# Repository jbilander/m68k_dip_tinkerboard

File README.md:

# 68k_dip_tinkerboard
A tinkerboard for the old Motorola 68k CPU

***

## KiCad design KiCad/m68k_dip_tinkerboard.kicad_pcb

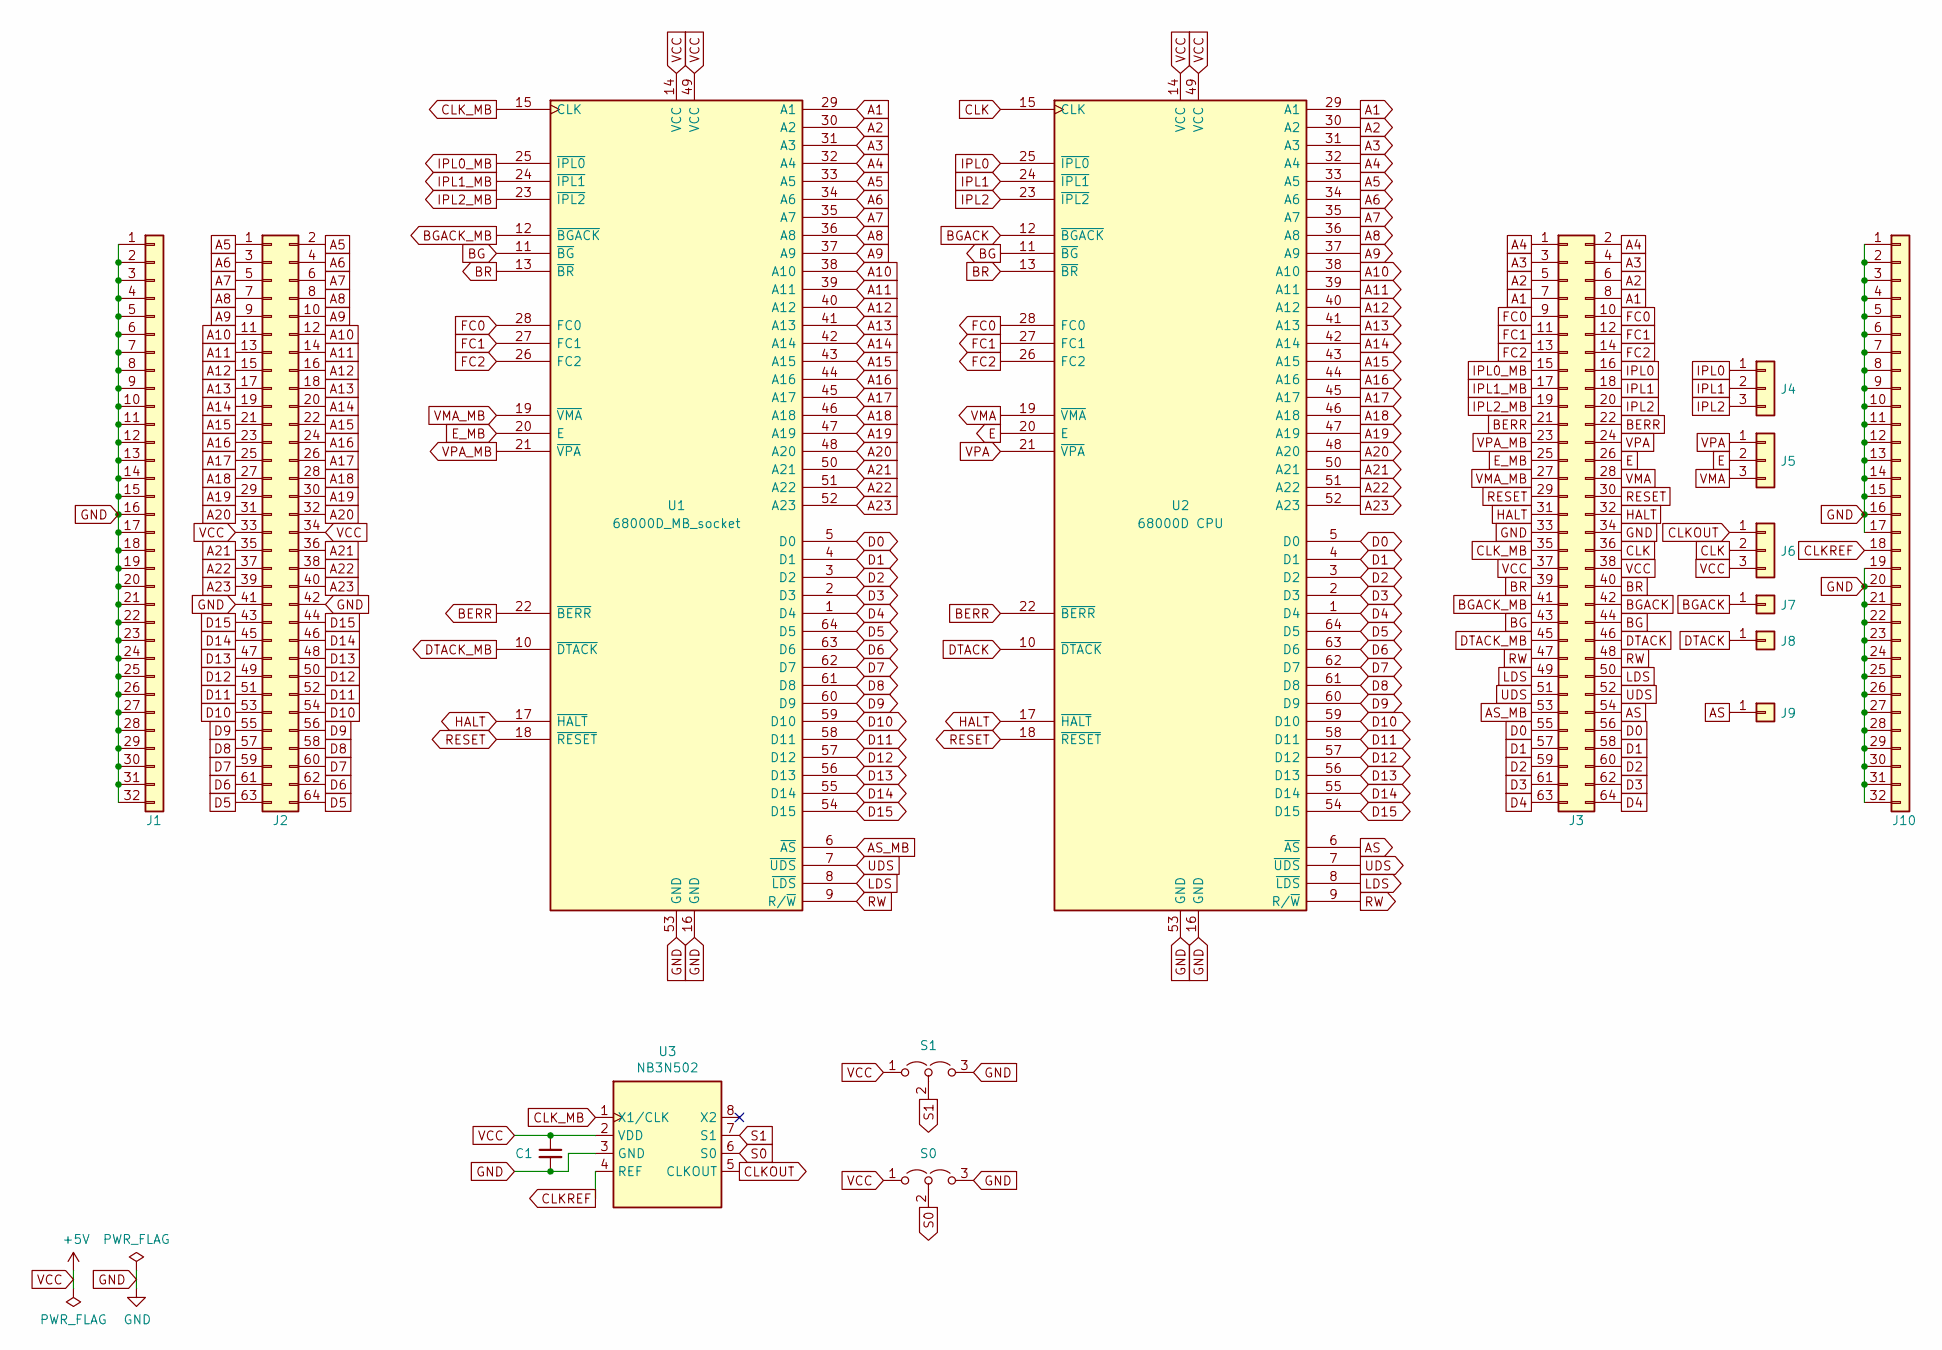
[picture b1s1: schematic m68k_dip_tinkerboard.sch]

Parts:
C1: C_Small; C_0805_2012Metric_Pad1.15x1.40mm_HandSolder
J1, J10: Conn_01x32; PinHeader_1x32_P2.54mm_Vertical
J2, J3: Conn_02x32_Odd_Even; PinHeader_2x32_P2.54mm_Vertical
J4, J5, J6: Conn_01x03; PinHeader_1x03_P2.54mm_Vertical
J7, J8, J9: Conn_01x01; PinHeader_1x01_P2.54mm_Vertical
S0, S1: Jumper_3_Open; PinHeader_1x03_P2.54mm_Vertical
U1: 68000D_MB_socket; DIP-64_W22.86mm_LongPads
U2: 68000D CPU; DIP-64_W22.86mm
U3: NB3N502; SOIC-8_3.9x4.9mm_P1.27mm

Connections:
A1: J3.7, J3.8, U1.29 (A1), U2.29 (A1)
A2: J3.5, J3.6, U1.30 (A2), U2.30 (A2)
A3: J3.3, J3.4, U1.31 (A3), U2.31 (A3)
A4: J3.1, J3.2, U1.32 (A4), U2.32 (A4)
A5: J2.1, J2.2, U1.33 (A5), U2.33 (A5)
A6: J2.3, J2.4, U1.34 (A6), U2.34 (A6)
A7: J2.5, J2.6, U1.35 (A7), U2.35 (A7)
A8: J2.7, J2.8, U1.36 (A8), U2.36 (A8)
A9: J2.9, J2.10, U1.37 (A9), U2.37 (A9)
A10: J2.11, J2.12, U1.38 (A10), U2.38 (A10)
A11: J2.13, J2.14, U1.39 (A11), U2.39 (A11)
A12: J2.15, J2.16, U1.40 (A12), U2.40 (A12)
A13: J2.17, J2.18, U1.41 (A13), U2.41 (A13)
A14: J2.19, J2.20, U1.42 (A14), U2.42 (A14)
A15: J2.21, J2.22, U1.43 (A15), U2.43 (A15)
A16: J2.23, J2.24, U1.44 (A16), U2.44 (A16)
A17: J2.25, J2.26, U1.45 (A17), U2.45 (A17)
A18: J2.27, J2.28, U1.46 (A18), U2.46 (A18)
A19: J2.29, J2.30, U1.47 (A19), U2.47 (A19)
A20: J2.31, J2.32, U1.48 (A20), U2.48 (A20)
A21: J2.35, J2.36, U1.50 (A21), U2.50 (A21)
A22: J2.37, J2.38, U1.51 (A22), U2.51 (A22)
A23: J2.39, J2.40, U1.52 (A23), U2.52 (A23)
AS: J3.54, J9.1, U2.6 (~AS)
AS_MB: J3.53, U1.6 (~AS)
BERR: J3.21, J3.22, U1.22 (~BERR), U2.22 (~BERR)
BG: J3.43, J3.44, U1.11 (~BG), U2.11 (~BG)
BGACK: J3.42, J7.1, U2.12 (~BGACK)
BGACK_MB: J3.41, U1.12 (~BGACK)
BR: J3.39, J3.40, U1.13 (~BR), U2.13 (~BR)
CLK: J3.36, J6.2, U2.15 (CLK)
CLKOUT: J6.1, U3.5 (CLKOUT)
CLKREF: J10.18, U3.4 (REF)
CLK_MB: J3.35, U1.15 (CLK), U3.1 (X1/CLK)
D0: J3.55, J3.56, U1.5 (D0), U2.5 (D0)
D1: J3.57, J3.58, U1.4 (D1), U2.4 (D1)
D2: J3.59, J3.60, U1.3 (D2), U2.3 (D2)
D3: J3.61, J3.62, U1.2 (D3), U2.2 (D3)
D4: J3.63, J3.64, U1.1 (D4), U2.1 (D4)
D5: J2.63, J2.64, U1.64 (D5), U2.64 (D5)
D6: J2.61, J2.62, U1.63 (D6), U2.63 (D6)
D7: J2.59, J2.60, U1.62 (D7), U2.62 (D7)
D8: J2.57, J2.58, U1.61 (D8), U2.61 (D8)
D9: J2.55, J2.56, U1.60 (D9), U2.60 (D9)
D10: J2.53, J2.54, U1.59 (D10), U2.59 (D10)
D11: J2.51, J2.52, U1.58 (D11), U2.58 (D11)
D12: J2.49, J2.50, U1.57 (D12), U2.57 (D12)
D13: J2.47, J2.48, U1.56 (D13), U2.56 (D13)
D14: J2.45, J2.46, U1.55 (D14), U2.55 (D14)
D15: J2.43, J2.44, U1.54 (D15), U2.54 (D15)
DTACK: J3.46, J8.1, U2.10 (~DTACK)
DTACK_MB: J3.45, U1.10 (~DTACK)
E: J3.26, J5.2, U2.20 (E)
E_MB: J3.25, U1.20 (E)
FC0: J3.9, J3.10, U1.28 (FC0), U2.28 (FC0)
FC1: J3.11, J3.12, U1.27 (FC1), U2.27 (FC1)
FC2: J3.13, J3.14, U1.26 (FC2), U2.26 (FC2)
GND: C1.2, J1.1, J1.2, J1.3, J1.4, J1.5, J1.6, J1.7, J1.8, J1.9, J1.10, J1.11, J1.12, J1.13, J1.14, J1.15, J1.16, J1.17, J1.18, J1.19, J1.20, J1.21, J1.22, J1.23, J1.24, J1.25, J1.26, J1.27, J1.28, J1.29, J1.30, J1.31, J1.32, J2.41, J2.42, J3.33, J3.34, J10.1, J10.2, J10.3, J10.4, J10.5, J10.6, J10.7, J10.8, J10.9, J10.10, J10.11, J10.12, J10.13, J10.14, J10.15, J10.16, J10.17, J10.19, J10.20, J10.21, J10.22, J10.23, J10.24, J10.25, J10.26, J10.27, J10.28, J10.29, J10.30, J10.31, J10.32, S0.3 (B), S1.3 (B), U1.16 (GND), U1.53 (GND), U2.16 (GND), U2.53 (GND), U3.3 (GND)
HALT: J3.31, J3.32, U1.17 (~HALT), U2.17 (~HALT)
IPL0: J3.16, J4.1, U2.25 (~IPL0)
IPL0_MB: J3.15, U1.25 (~IPL0)
IPL1: J3.18, J4.2, U2.24 (~IPL1)
IPL1_MB: J3.17, U1.24 (~IPL1)
IPL2: J3.20, J4.3, U2.23 (~IPL2)
IPL2_MB: J3.19, U1.23 (~IPL2)
LDS: J3.49, J3.50, U1.8 (~LDS), U2.8 (~LDS)
RESET: J3.29, J3.30, U1.18 (~RESET), U2.18 (~RESET)
RW: J3.47, J3.48, U1.9 (R/~W), U2.9 (R/~W)
S0: S0.2 (C), U3.6 (S0)
S1: S1.2 (C), U3.7 (S1)
UDS: J3.51, J3.52, U1.7 (~UDS), U2.7 (~UDS)
VCC: C1.1, J2.33, J2.34, J3.37, J3.38, J6.3, S0.1 (A), S1.1 (A), U1.14 (VCC), U1.49 (VCC), U2.14 (VCC), U2.49 (VCC), U3.2 (VDD)
VMA: J3.28, J5.3, U2.19 (~VMA)
VMA_MB: J3.27, U1.19 (~VMA)
VPA: J3.24, J5.1, U2.21 (~VPA)
VPA_MB: J3.23, U1.21 (~VPA)

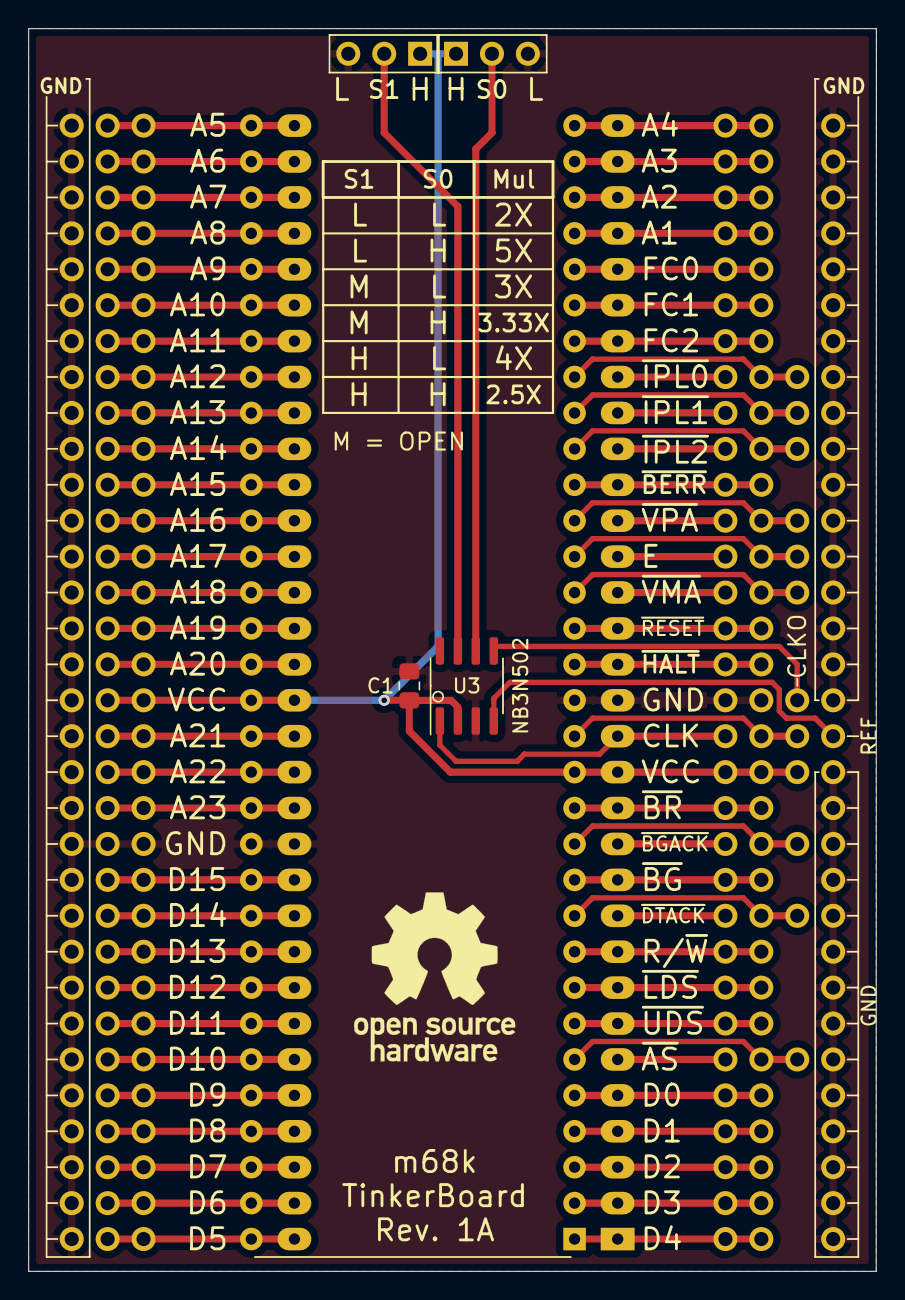
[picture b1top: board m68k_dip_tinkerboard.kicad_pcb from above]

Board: 2 copper layers, 60.0 x 87.9 mm, 16 parts (0 on the bottom side), 76 nets.

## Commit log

2021-03-14 added files
2021-03-14 added schematic rev1a pdf
2021-03-14 added gerbers
2021-03-14 added images
